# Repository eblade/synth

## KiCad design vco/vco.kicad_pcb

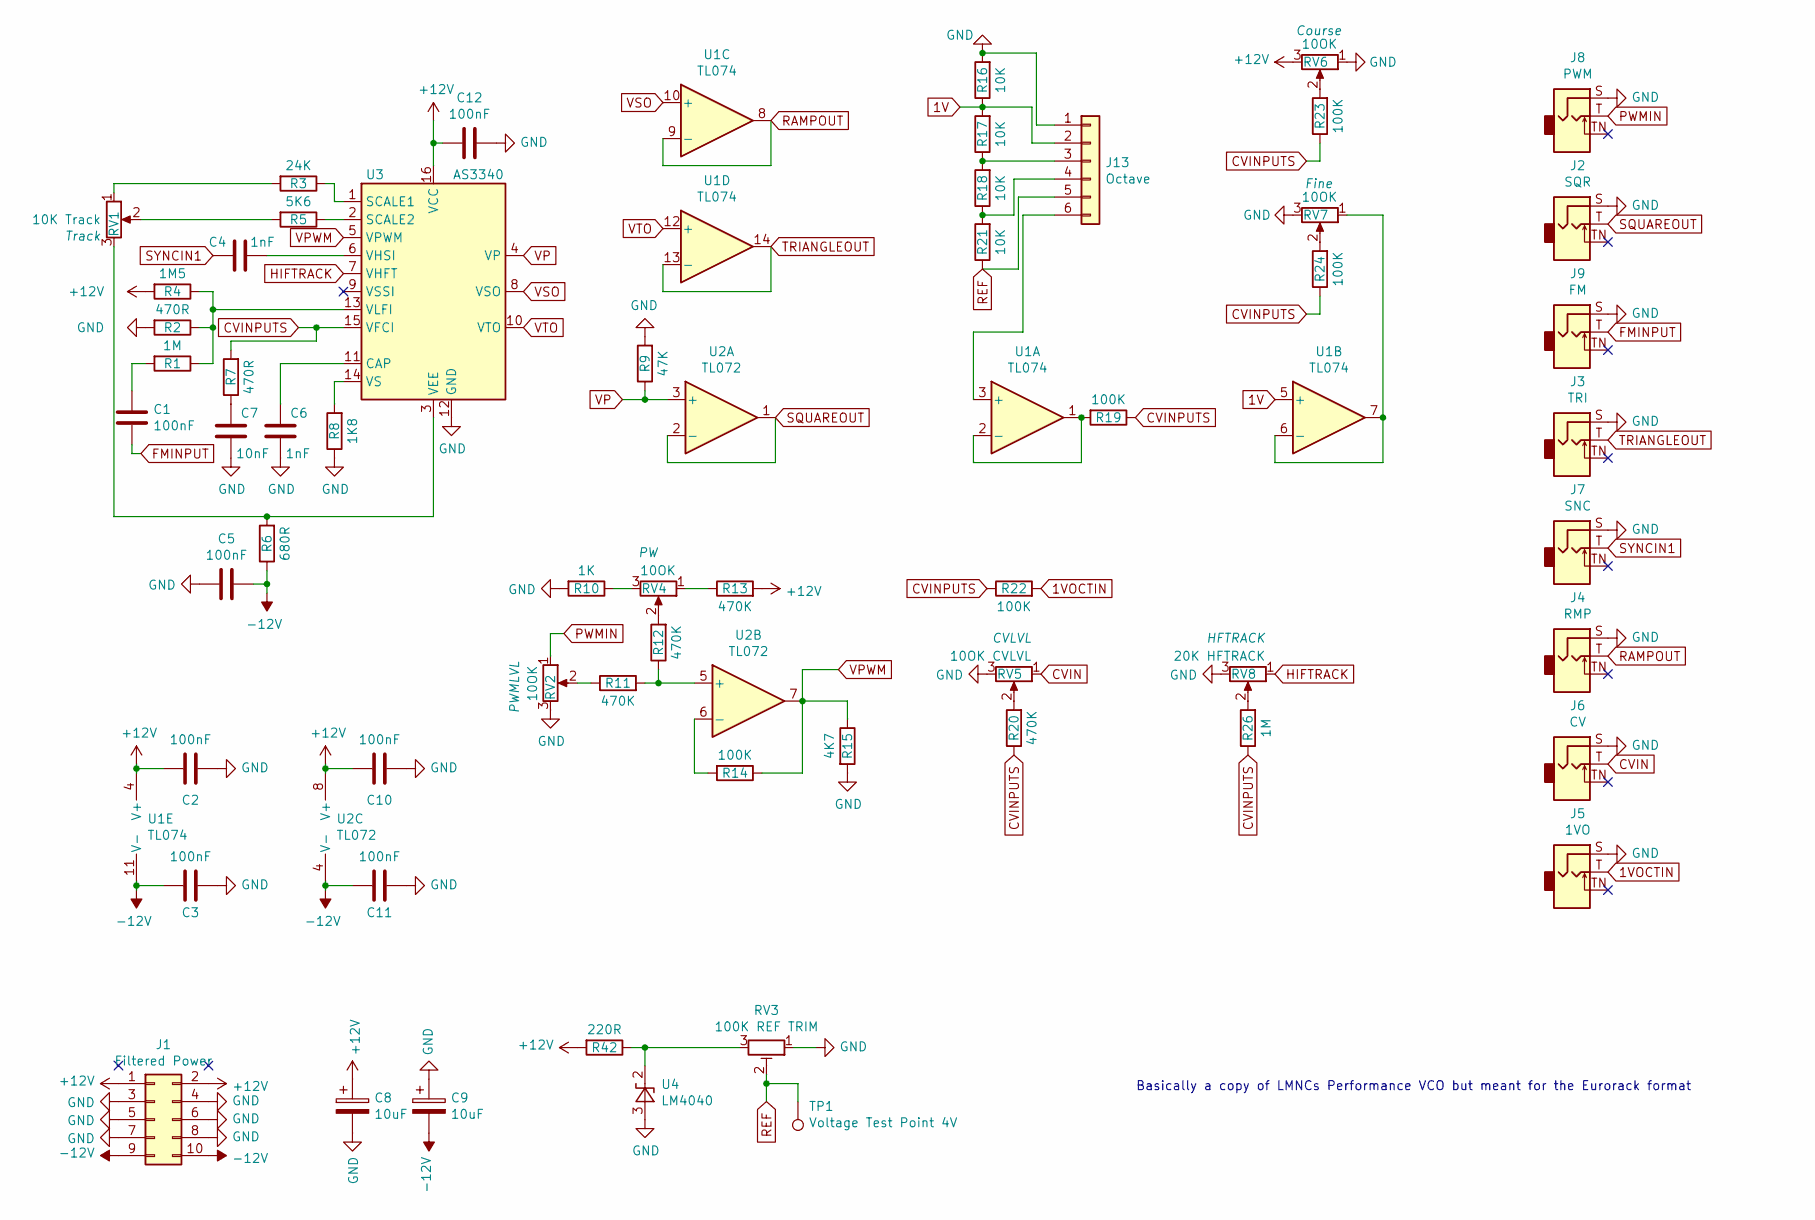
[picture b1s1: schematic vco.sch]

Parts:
C1, C2, C3, C5, C10, C11, C12: 100nF; C_Disc_D3.0mm_W1.6mm_P2.50mm
C4, C6: 1nF; C_Disc_D3.0mm_W1.6mm_P2.50mm
C7: 10nF; C_Disc_D3.0mm_W1.6mm_P2.50mm
C8, C9: 10uF; CP_Radial_D5.0mm_P2.50mm
J1: Filtered Power; PinHeader_2x05_P2.54mm_Vertical
J2: SQR; Jack_3.5mm_QingPu_WQP-PJ398SM_Vertical_CircularHoles
J3: TRI; Jack_3.5mm_QingPu_WQP-PJ398SM_Vertical_CircularHoles
J4: RMP; Jack_3.5mm_QingPu_WQP-PJ398SM_Vertical_CircularHoles
J5: 1VO; Jack_3.5mm_QingPu_WQP-PJ398SM_Vertical_CircularHoles
J6: CV; Jack_3.5mm_QingPu_WQP-PJ398SM_Vertical_CircularHoles
J7: SNC; Jack_3.5mm_QingPu_WQP-PJ398SM_Vertical_CircularHoles
J8: PWM; Jack_3.5mm_QingPu_WQP-PJ398SM_Vertical_CircularHoles
J9: FM; Jack_3.5mm_QingPu_WQP-PJ398SM_Vertical_CircularHoles
J13: Octave; PinHeader_1x06_P2.54mm_Vertical
R1, R26: 1M; R_Axial_DIN0204_L3.6mm_D1.6mm_P7.62mm_Horizontal
R2, R7: 470R; R_Axial_DIN0204_L3.6mm_D1.6mm_P7.62mm_Horizontal
R3: 24K; R_Axial_DIN0204_L3.6mm_D1.6mm_P7.62mm_Horizontal
R4: 1M5; R_Axial_DIN0204_L3.6mm_D1.6mm_P7.62mm_Horizontal
R5: 5K6; R_Axial_DIN0204_L3.6mm_D1.6mm_P7.62mm_Horizontal
R6: 680R; R_Axial_DIN0204_L3.6mm_D1.6mm_P7.62mm_Horizontal
R8: 1K8; R_Axial_DIN0204_L3.6mm_D1.6mm_P7.62mm_Horizontal
R9: 47K; R_Axial_DIN0204_L3.6mm_D1.6mm_P7.62mm_Horizontal
R10: 1K; R_Axial_DIN0204_L3.6mm_D1.6mm_P7.62mm_Horizontal
R11, R12, R13, R20: 470K; R_Axial_DIN0204_L3.6mm_D1.6mm_P7.62mm_Horizontal
R14, R19, R22, R23, R24: 100K; R_Axial_DIN0204_L3.6mm_D1.6mm_P7.62mm_Horizontal
R15: 4K7; R_Axial_DIN0204_L3.6mm_D1.6mm_P7.62mm_Horizontal
R16, R17, R18, R21: 10K; R_Axial_DIN0204_L3.6mm_D1.6mm_P7.62mm_Horizontal
R42: 220R; R_Axial_DIN0204_L3.6mm_D1.6mm_P7.62mm_Horizontal
RV1: 10K Track; TRIM_3296W-1-250
RV2, RV4, RV6, RV7: 10OK; Potentiometer_Alps_RK09L_Single_Vertical
RV3: 100K REF TRIM; TRIM_3296W-1-250
RV5: 10OK CVLVL; TRIM_3296W-1-250
RV8: 20K HFTRACK; TRIM_3296W-1-250
TP1: Voltage Test Point 4V; TestPoint_Pad_D3.0mm
U1: TL074; DIP-14_W7.62mm_Socket
U2: TL072; DIP-8_W7.62mm_Socket
U3: AS3340; DIP-16_W7.62mm_Socket
U4: LM4040; TO-92

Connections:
1V: J13.2, R16.1, R17.2, U1.5 (+)
1VOCTIN: J5.T, R22.2
+12V: C2.2, C8.1, C10.2, C12.2, J1.1, J1.2, R4.2, R13.2, R42.2, RV6.3, U1.4 (V+), U2.8 (V+), U3.16 (VCC)
-12V: C3.2, C5.1, C9.2, C11.2, J1.9, J1.10, R6.1, U1.11 (V-), U2.4 (V-)
CVIN: J6.T, RV5.1
CVINPUTS: R7.2, R19.1, R20.1, R22.1, R23.1, R24.1, R26.1, U3.15 (VFCI)
FMINPUT: C1.1, J9.T
GND: C2.1, C3.1, C5.2, C6.1, C7.1, C8.2, C9.1, C10.1, C11.1, C12.1, J1.3, J1.4, J1.5, J1.6, J1.7, J1.8, J2.S, J3.S, J4.S, J5.S, J6.S, J7.S, J8.S, J9.S, J13.1, R2.2, R8.1, R9.2, R10.2, R15.2, R16.2, RV2.3, RV3.1, RV5.3, RV6.1, RV7.3, RV8.3, U3.12 (GND), U4.3 (A)
HIFTRACK: RV8.1, U3.7 (VHFT)
unnamed: C1.2, R1.2
unnamed: C4.1, U3.6 (VHSI)
unnamed: C6.2, U3.11 (CAP)
unnamed: C7.2, R7.1
unnamed: J13.3, R17.1, R18.2
unnamed: J13.4, R18.1, R21.2
unnamed: J13.6, U1.3 (+)
unnamed: R1.1, R2.1, R4.1, U3.13 (VLFI)
unnamed: R3.1, U3.1 (SCALE1)
unnamed: R3.2, RV1.1
unnamed: R5.1, U3.2 (SCALE2)
unnamed: R5.2, RV1.2
unnamed: R6.2, RV1.3, U3.3 (VEE)
unnamed: R8.2, U3.14 (VS)
unnamed: R10.1, RV4.3
unnamed: R11.1, RV2.2
unnamed: R11.2, R12.1, U2.5 (+)
unnamed: R12.2, RV4.2
unnamed: R13.1, RV4.1
unnamed: R14.2, U2.6 (-)
unnamed: R19.2, U1.1, U1.2 (-)
unnamed: R20.2, RV5.2
unnamed: R23.2, RV6.2
unnamed: R24.2, RV7.2
unnamed: R26.2, RV8.2
unnamed: R42.1, RV3.3, U4.2 (K)
unnamed: RV7.1, U1.6 (-), U1.7
PWMIN: J8.T, RV2.1
RAMPOUT: J4.T, U1.8, U1.9 (-)
REF: J13.5, R21.1, RV3.2, TP1.1
SQUAREOUT: J2.T, U2.1, U2.2 (-)
SYNCIN1: C4.2, J7.T
TRIANGLEOUT: J3.T, U1.13 (-), U1.14
VP: R9.1, U2.3 (+), U3.4 (VP)
VPWM: R14.1, R15.1, U2.7, U3.5 (VPWM)
VSO: U1.10 (+), U3.8 (VSO)
VTO: U1.12 (+), U3.10 (VTO)

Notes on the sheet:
Basically a copy of LMNCs Performance VCO but meant for the Eurorack format

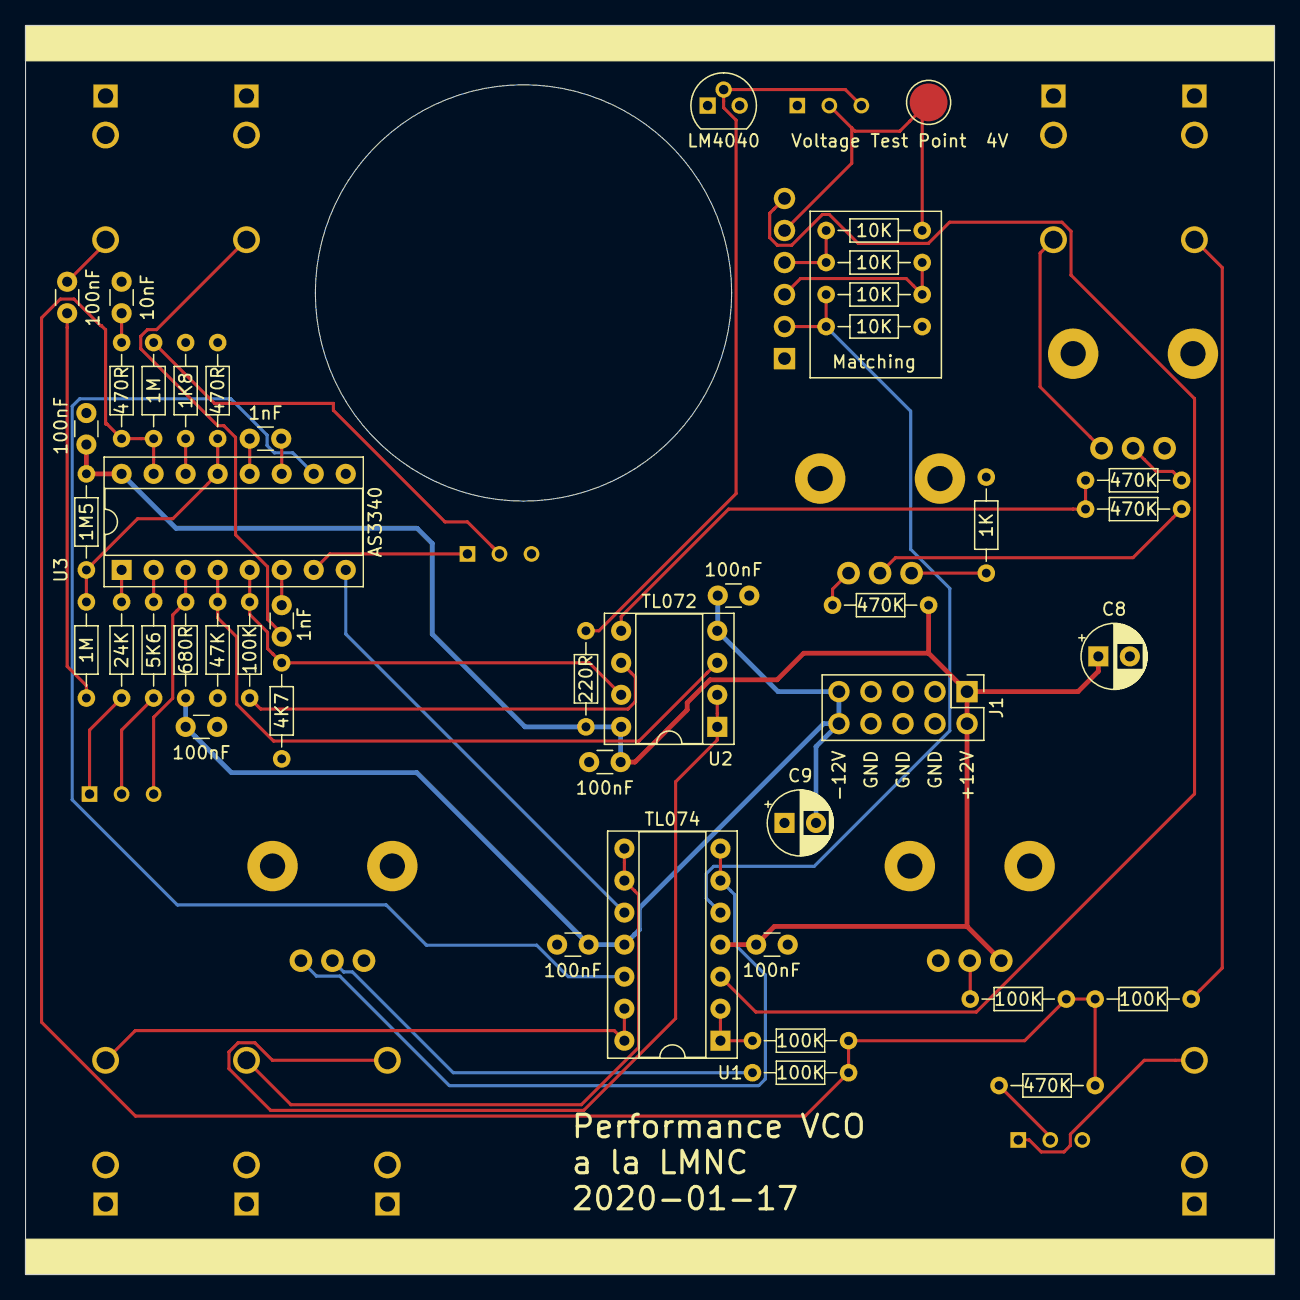
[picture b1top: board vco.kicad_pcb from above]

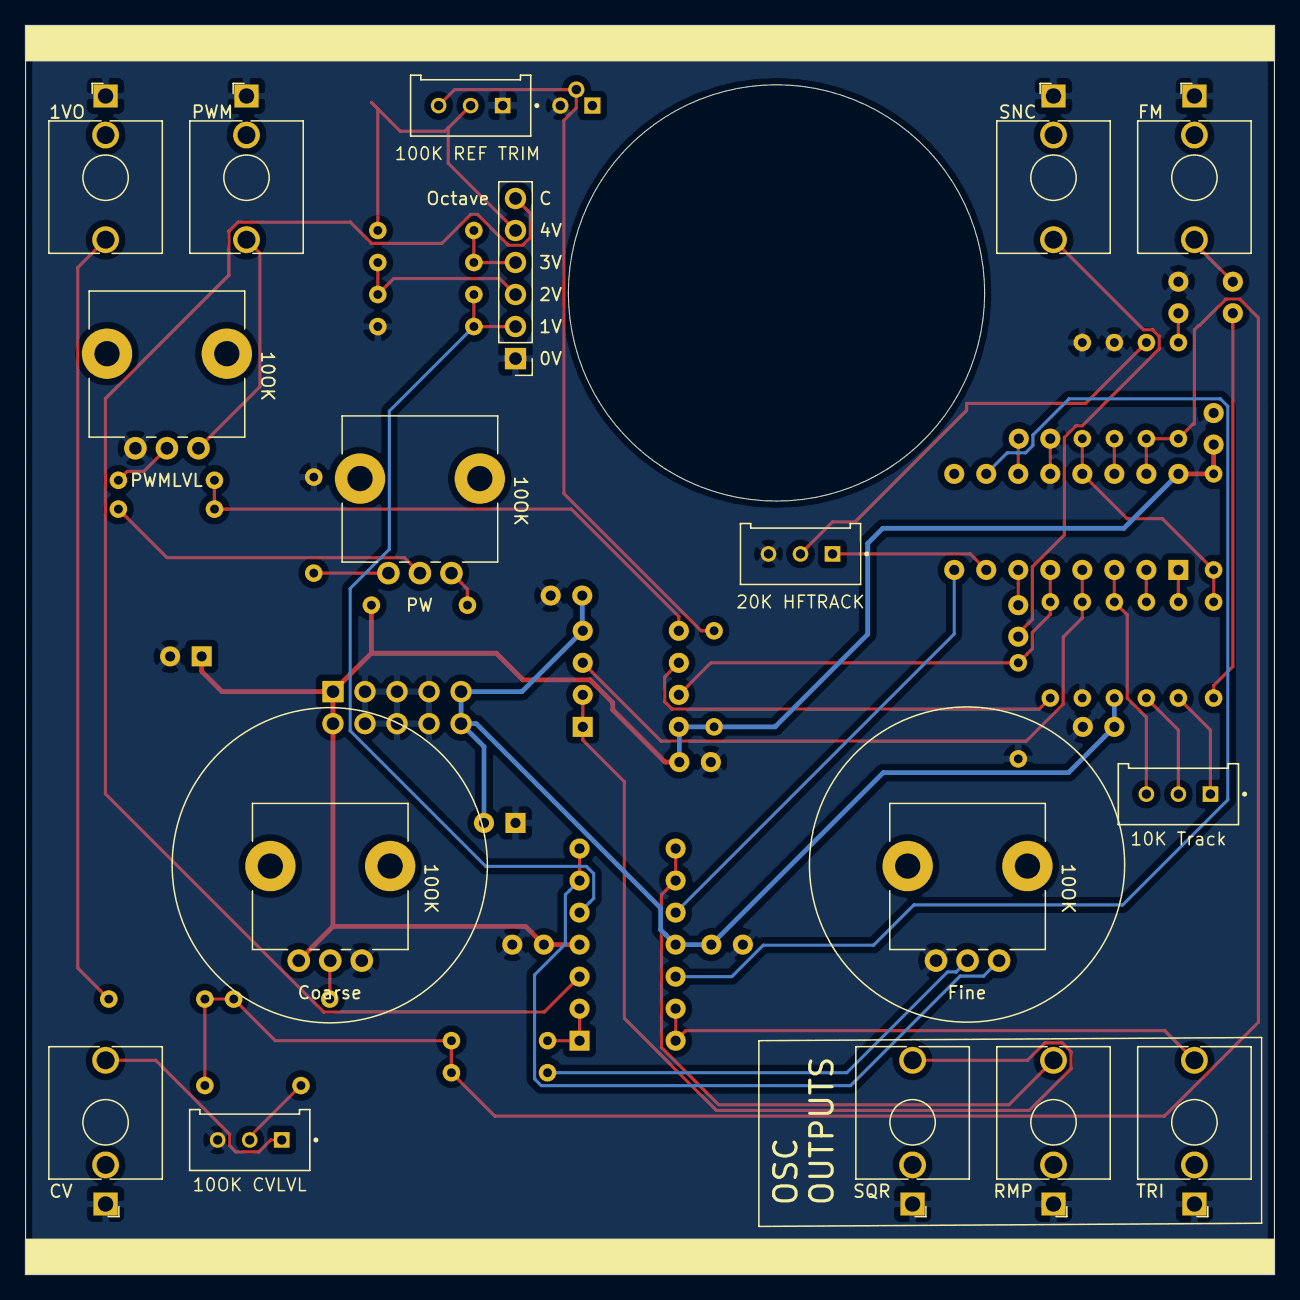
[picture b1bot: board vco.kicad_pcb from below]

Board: 2 copper layers, 99.1 x 99.1 mm, 61 parts (17 on the bottom side), 46 nets.
